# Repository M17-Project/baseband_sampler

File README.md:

# baseband_sampler
Arduino shield sized baseband sampler. It uses an STM32 F303RE Nucleo board and communicates over USB-UART (230400 baud, 8n1).

## What does it do?
The shield board contains:
- **MCP33131-10-E/MS** 16-bit 1Msps ADC converter,
- **LM4120AIM5-2.5** 2.5V reference,
- **LDL1117S18R** 1.8V low-drop voltage regulator.

The working principle is simple. After being interrogated by the host PC, by sending a single byte over UART, the device collects 19,200 samples of the signal presented at the `Input` port. The sampling trigger signal has to be provided by the user as a TTL signal at the `Trig` port. Every rising edge starts a conversion. After all samples are collected, all the data is sent to a PC as a string of `uint16_t` values.<br>
At the power-up, the ADC performs a calibration sequence taking approximately 500 ms. The blue button on the Nucleo can be used to force re-calibration when the user needs it (significant ambient temperature change etc.). Pressing the button initializes the same sequence.

## Contents
- `CubeIDE` - a complete CubeIDE project, this is where the source code is
- `EAGLE` - the schematic and PCB design files (EAGLE 7.7.0) along with zipped gerbers (tailored for JLCPCB).
- `Matlab` contains a demo Matlab application

## Demo Matlab application
Hit the `Start` button to send the acquisition command to the board. After a few seconds you should see the eye plot.

## References
- [MCP33111 family datasheet](https://ww1.microchip.com/downloads/en/DeviceDoc/MCP33131-MCP33121-MCP33111-Family-Data-Sheet-DS20006122A.pdf)

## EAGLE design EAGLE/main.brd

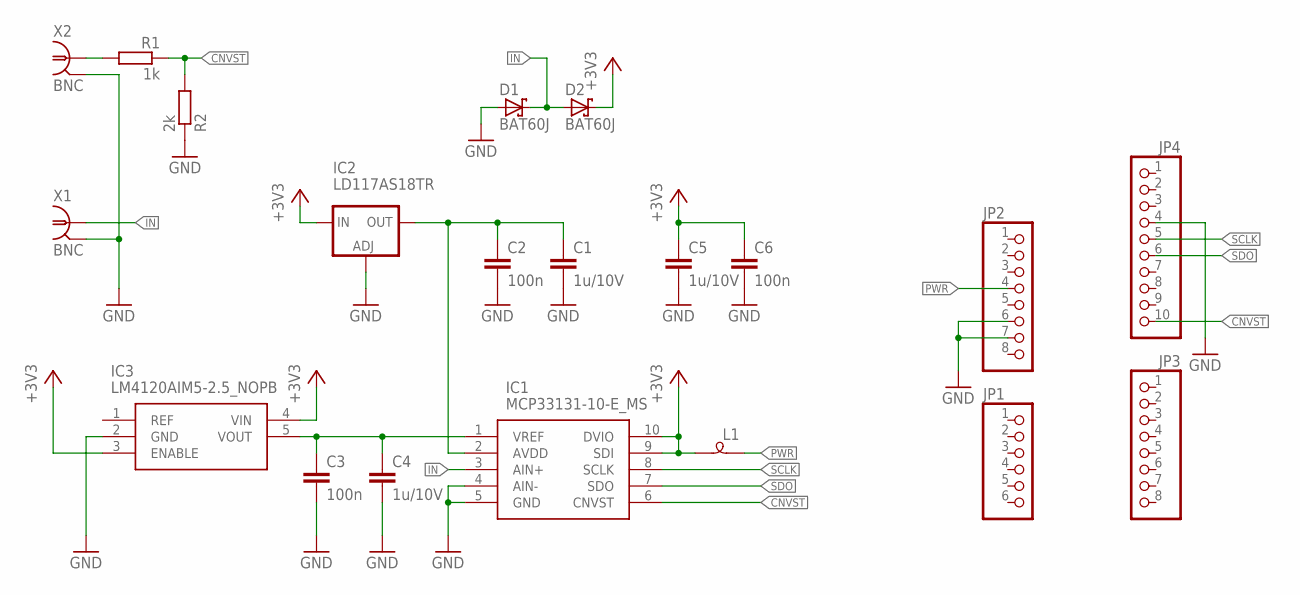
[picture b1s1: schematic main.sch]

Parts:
C1, C4, C5: 1u/10V; C1206
C2, C3, C6: 100n; C0805
D1, D2: BAT60J; SOD323_ST
IC1: MCP33131-10-E_MS; SOP50P490X110-10N
IC2: LD117AS18TR; SOT223
IC3: LM4120AIM5-2.5_NOPB; SOT95P280X145-5N
JP1: PINHD-1X6; 1X06
JP2, JP3: PINHD-1X8; 1X08
JP4: PINHD-1X10; 1X10
L1: SM-B5
R1: 1k; R0805
R2: 2k; R0805
X1, X2: BNC; AMP_227161

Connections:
+3V3: C5.1, C6.1, D2.C, IC1.9 (SDI), IC1.10 (DVIO), IC2.3 (IN), IC3.3 (ENABLE), IC3.4 (VIN), L1.2
CNVST: IC1.6 (CNVST), JP4.10, R1.1, R2.2
GND: C1.2, C2.2, C3.2, C4.2, C5.2, C6.2, D1.A, IC1.4 (AIN-), IC1.5 (GND), IC2.1 (ADJ), IC3.2 (GND), JP2.6, JP2.7, JP4.4, R2.1, X1.2, X2.2
IN: D1.C, D2.A, IC1.3 (AIN+), X1.1
unnamed: C3.1, C4.1, IC1.1 (VREF), IC3.5 (VOUT)
unnamed: C1.1, C2.1, IC1.2 (AVDD), IC2.4 (OUT)
unnamed: R1.2, X2.1
PWR: JP2.4, L1.1
SCLK: IC1.8 (SCLK), JP4.5
SDO: IC1.7 (SDO), JP4.6

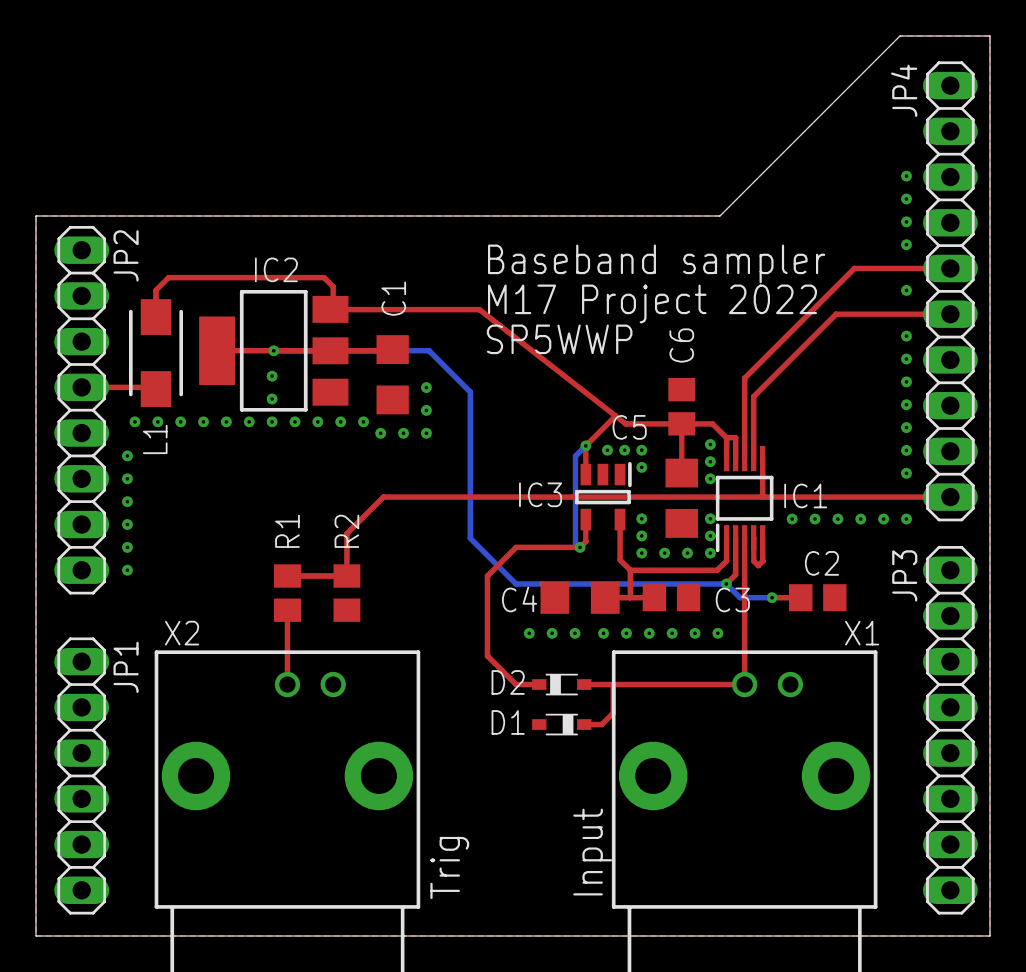
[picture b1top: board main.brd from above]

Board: 2 copper layers, 53.0 x 50.0 mm, 20 parts (0 on the bottom side), 10 nets.

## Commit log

2022-10-18 Add files via upload
    schematic - PDF
